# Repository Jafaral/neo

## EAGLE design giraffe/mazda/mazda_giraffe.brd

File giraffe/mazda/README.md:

Mazda giraffe
=============

The Switches
------------

```
                               Switches
                              OFF <=> ON
                       ___________________________  
                   ---|       1  [->O]       +12v |----|__
     Car Connector |  |       2  [->O]      CAN H |----|  |  to CAM
                   ---|       3  [->O]      CAN L |----|__|
                      |       4  [->O]       -GND |----|
                      |            -R-            | 
                      |        /---------\        |
                      |       /   OBDII   \       |
                      | O |-_/_____________\_____ |
Optional External Power ^
```
1. Power the panda from the car
2. Hardware Passthru Stock CAM
3. Connect Panda's CAN1 to CAM CAN
4. Feed 12V to Panda's ignition pin

WARNING WARNING WARNING! Choose between powering the Panda from the car (switch #1) or via external power. Never connect external power if you have the first switch #1 at the ON poistion. You have been warned! Otherwise your car will be transported into another galaxy without you! 

### Switch settings (assuming no external power):

#### Recommended Giraffe Settings

+ 1111 All ON (Best Setting)
  Typically you want to cuttoff stock CAM and let the panda decides what CAN msgs to pass and what to drop,
  but I discovered OP steering doesn't get affected even if I let stock LKAS msgs to pass since we are 
  sending LKAS msgs at much higher rate than stock. 
  
  With this setting the Car is always happy (no dashboard warnings) regardless of whether OP is running or not when you start the car. If EON is off you can start the car and start driving, once EON is up, OP will be available to use.

+ 1011 :  CAM CAN <=> panda CAN3, panda CAN1 <=> CAR CAN1

      Note: With this setting you have to start the car's ignition, and then turn 
      it off immediatly (without pressing on the brakes, push the start button 
      three times). wait for OP to start and then turn the car normally. With this
      mode, you are guaranteed no to have any interference from stock LKAS
      (see comment at the bottom). 
   
   With the second, I recommend flashing the panda with safety model set to Mazda. This allows you just turn on the car and go if EON is not connected. 

#### Stock
+ 0100 :  CAM is Stock (hardware passthru), panda is OFF (no power to panda/eon)
+ 1100 :  CAM is Stock (hardware passthru), panda is ON , Panda CAN1 <=> CAR CAN1
+ 1110 :  CAM is Stock (hardware passthru), panda is ON , Panda CAN1 <=> CAR CAN1, Panda CAN3 <=> CAM CAN (CAR CAN1),
       
       Note: Once powered panda is always conncted to CAR CAN1, since the CAM is
             in hardware passthru, the car's CAN1 msgs are also read on Panda's CAN3.
             effectively all CAN msgs are read  twice

#### Stock if Panda is flashed with default safety model set to Mazda
+ 1010 :  CAM CAN <=> panda CAN3, panda CAN1 <=> CAR CAN1

### Note

  If you power the panda from the car, it takes a couple of seconds to boot and have OP ready to talk to the car. By that time the car might detect that the camera is not connected (panda isn't forwarding msgs yet) and you might git dashboard errors. To avoid that problem, start the car in Accessory mode and turn it off right away. Do that by pressing the car's start button three times without depressing the brake. With Mazda cars, this will provide power for one minute, panda only needs a couple of seconds to boot and you can see OP ready on your EON's screen. Now you are ready to rumble!

Parts
-----

Switch           :https://www.digikey.com/product-detail/en/grayhill-inc/78F04T/GH7730-ND/2680797

Resistor         : https://www.digikey.com/product-detail/en/te-connectivity-passive-product/CRGH1206F120R/A129547CT-ND/8566751

Female connector : https://www.mouser.com/ProductDetail/538-34824-0124

Male Connector   : https://www.mouser.com/ProductDetail/538-34826-8124

Terminals        :  https://www.mouser.com/ProductDetail/538-560023-0548

OBDII Female connector, these are standard and you can order them form different places. The Ones I got are out of stock, but this is the same item:
https://www.aliexpress.com/item/OBD-16PIN-female-connector-OBD2-Female-Plug-J1962f/32711598516.html

And some wires!

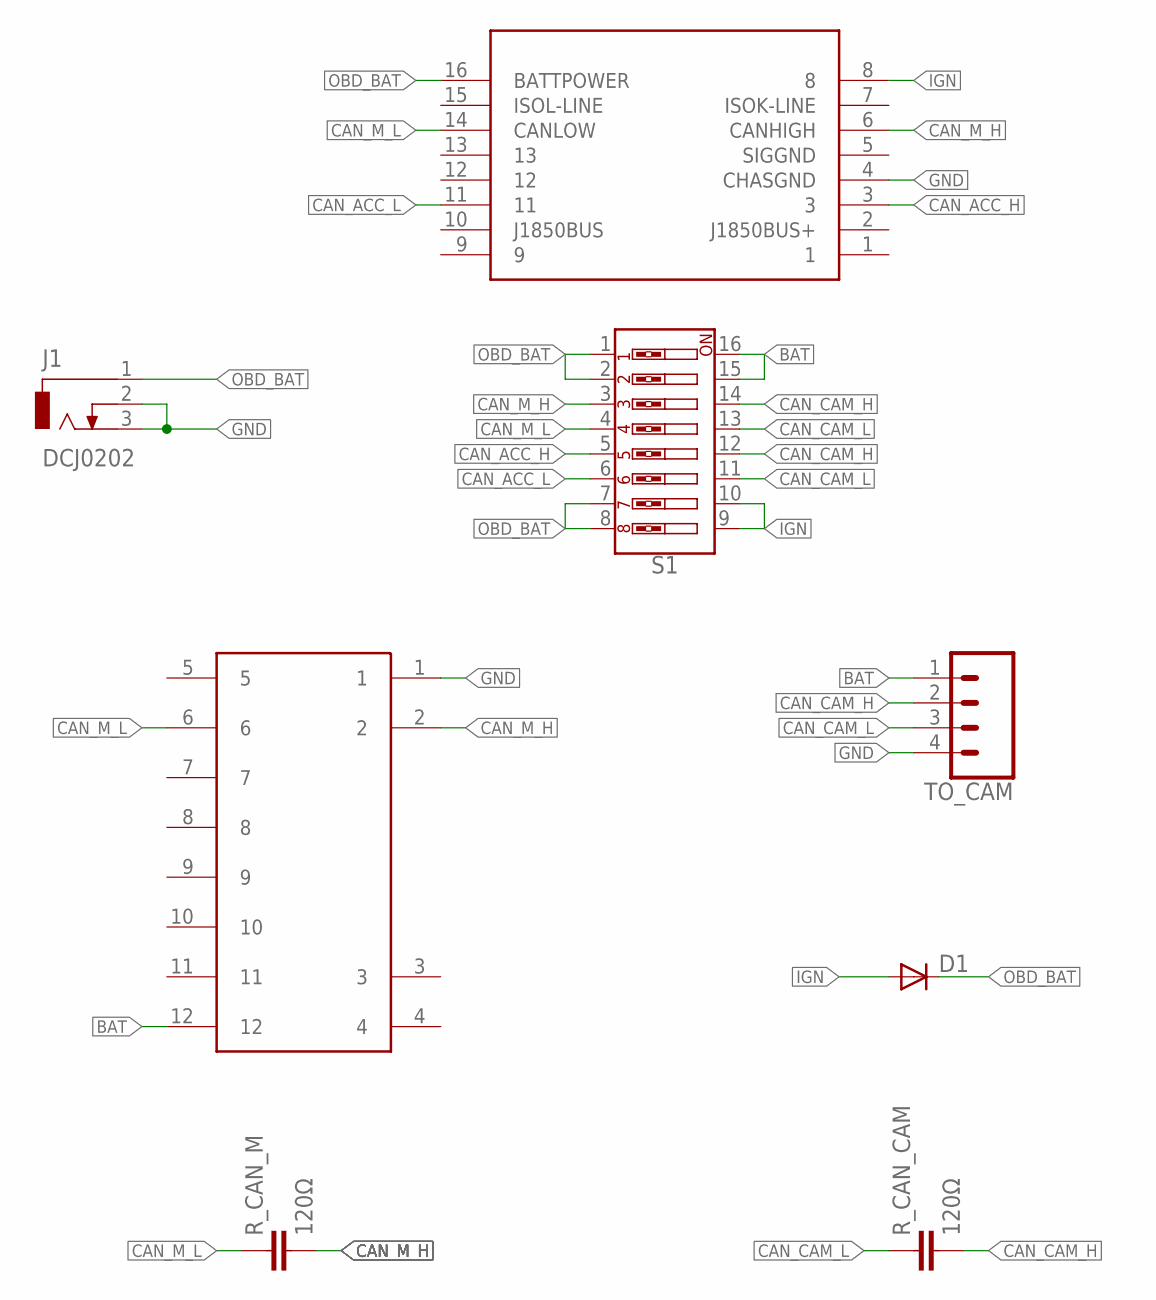
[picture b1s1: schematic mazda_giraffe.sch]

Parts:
D1: DIODE-DO-214AC; DO-214AC
J1: DCJ0202
OBD_II: OBDII
R_CAN_CAM: 120Ω; C1206
R_CAN_M: 120Ω; C1206
S1: DIP-08-PTH; DIPSWITCH-08
TO_CAM: CONN_04LONGPADS; 1X04_LONGPADS
TO_CAR: 34826-8124

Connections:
BAT: S1.15, S1.16, TO_CAM.1, TO_CAR.12
CAN_ACC_H: OBD_II.3, S1.5
CAN_ACC_L: OBD_II.11, S1.6
CAN_CAM_H: R_CAN_CAM.2, S1.12, S1.14, TO_CAM.2
CAN_CAM_L: R_CAN_CAM.1, S1.11, S1.13, TO_CAM.3
CAN_M_H: OBD_II.6 (CANHIGH), R_CAN_M.2, S1.3, TO_CAR.2
CAN_M_L: OBD_II.14 (CANLOW), R_CAN_M.1, S1.4, TO_CAR.6
GND: J1.2, J1.3, OBD_II.4 (CHASGND), TO_CAM.4, TO_CAR.1
IGN: D1.A, OBD_II.8, S1.9, S1.10
OBD_BAT: D1.C, J1.1, OBD_II.16 (BATTPOWER), S1.1, S1.2, S1.7, S1.8

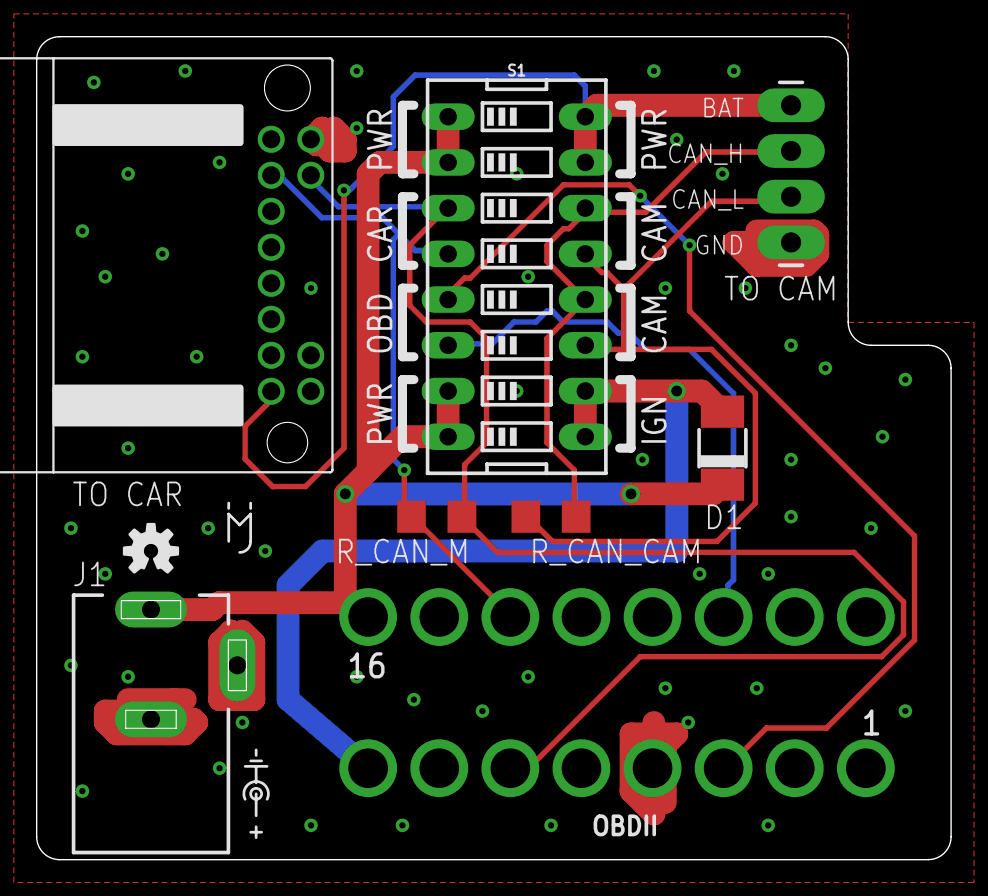
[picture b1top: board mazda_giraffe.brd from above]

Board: 2 copper layers, 50.8 x 45.7 mm, 10 parts (1 on the bottom side), 10 nets.

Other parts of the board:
U$1, U$2: OSHW-LOGO-S

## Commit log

2019-01-30 initial part list
2019-04-22 update the list
2019-04-22 add the giraffe board and update README
2019-09-23 Update with current giraffe info
2019-09-25 Source from digikey

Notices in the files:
parts and their libraries:
SparkFun-Connectors: Licensing: Creative Commons ShareAlike 4.0 International - https://creativecommons.org/licenses/by-sa/4.0
